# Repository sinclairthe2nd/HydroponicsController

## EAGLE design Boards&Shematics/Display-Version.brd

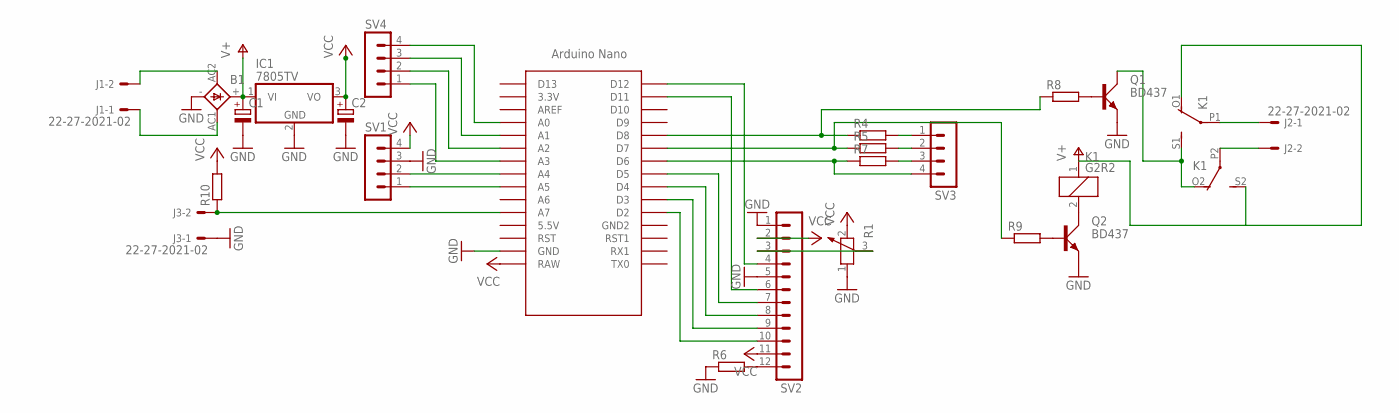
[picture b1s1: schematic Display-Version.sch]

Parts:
B1: FBU4
C1: CPOL-EUE3.5-10; E3,5-10
C2: CPOL-EUE2.5-6; E2,5-6
IC1: 7805TV; TO220V
J1, J2, J3: 22-27-2021-02; 6410-02
K1: G2R2
Q1, Q2: BD437; TO126AV
R1: POTENTIOMETER_PT-10S; PT-10S
R4, R5, R6, R7, R8, R9, R10: R-EU_R1206W; R1206W
SV1, SV3, SV4: MA04-1
SV2: MA12-1
U$1: NANO

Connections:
GND: B1.-, C1.-, C2.-, IC1.2 (GND), J3.1, Q1.E, Q2.E, R1.1, R6.1, SV1.3, SV2.1, SV2.5, U$1.GND
unnamed: R6.2, SV2.12
unnamed: R4.1, R8.1, U$1.D8
unnamed: B1.AC2 (AC1), J1.2
unnamed: B1.AC1 (AC2), J1.1
unnamed: R5.1, R9.1, U$1.D7
unnamed: R4.2, SV3.1
unnamed: R7.1, SV3.4, U$1.D6
unnamed: R5.2, SV3.2
unnamed: R7.2, SV3.3
unnamed: J2.1, K1.P1
unnamed: J2.2, K1.P2
unnamed: Q1.B, R8.2
unnamed: K1.2, Q2.C
unnamed: Q2.B, R9.2
unnamed: SV2.10, U$1.D2
unnamed: SV2.9, U$1.D3
unnamed: SV2.8, U$1.D4
unnamed: SV2.7, U$1.D5
unnamed: SV2.6, U$1.D11
unnamed: SV2.4, U$1.D12
unnamed: R1.3, SV2.3
unnamed: SV1.1, U$1.A5
unnamed: K1.O2 (O), K1.S1 (S), Q1.C
unnamed: SV1.2, U$1.A4
unnamed: SV4.1, U$1.A3
unnamed: J3.2, R10.1, U$1.A7
unnamed: SV4.2, U$1.A2
unnamed: SV4.3, U$1.A1
unnamed: SV4.4, U$1.A0
V+: B1.+, C1.+, IC1.1 (VI), K1.1, K1.O1 (O), K1.S2 (S)
VCC: C2.+, IC1.3 (VO), R1.2, R10.2, SV1.4, SV2.2, SV2.11, U$1.RAW

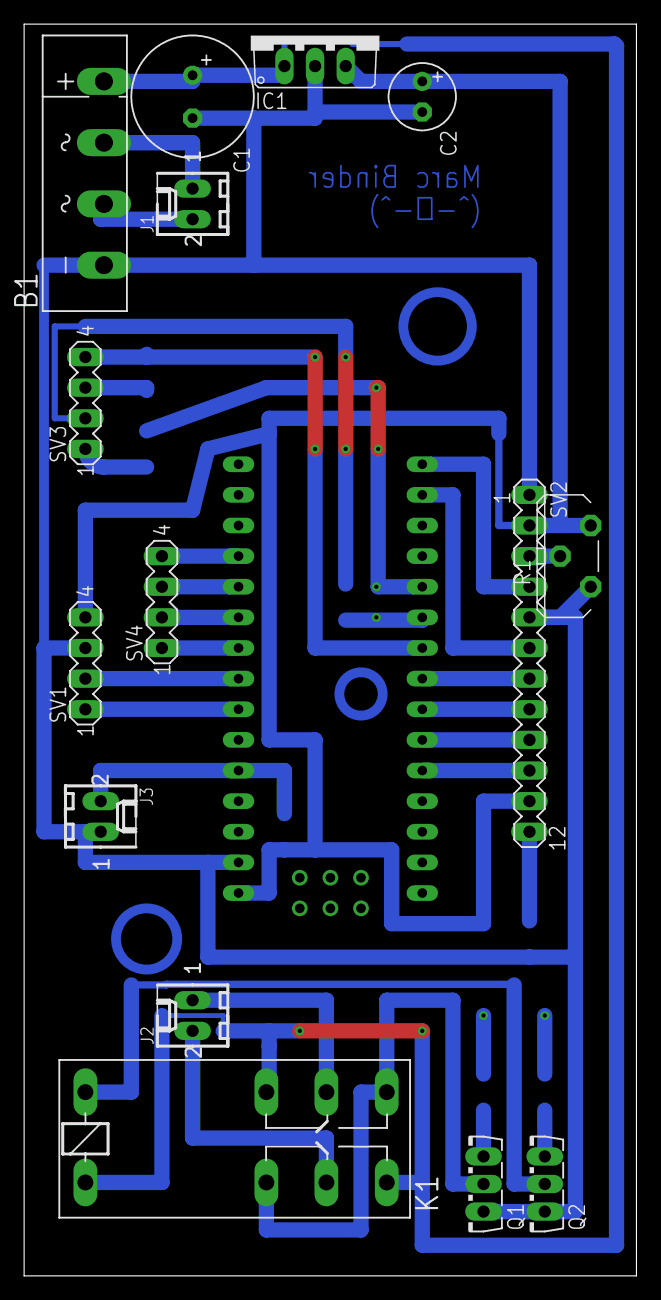
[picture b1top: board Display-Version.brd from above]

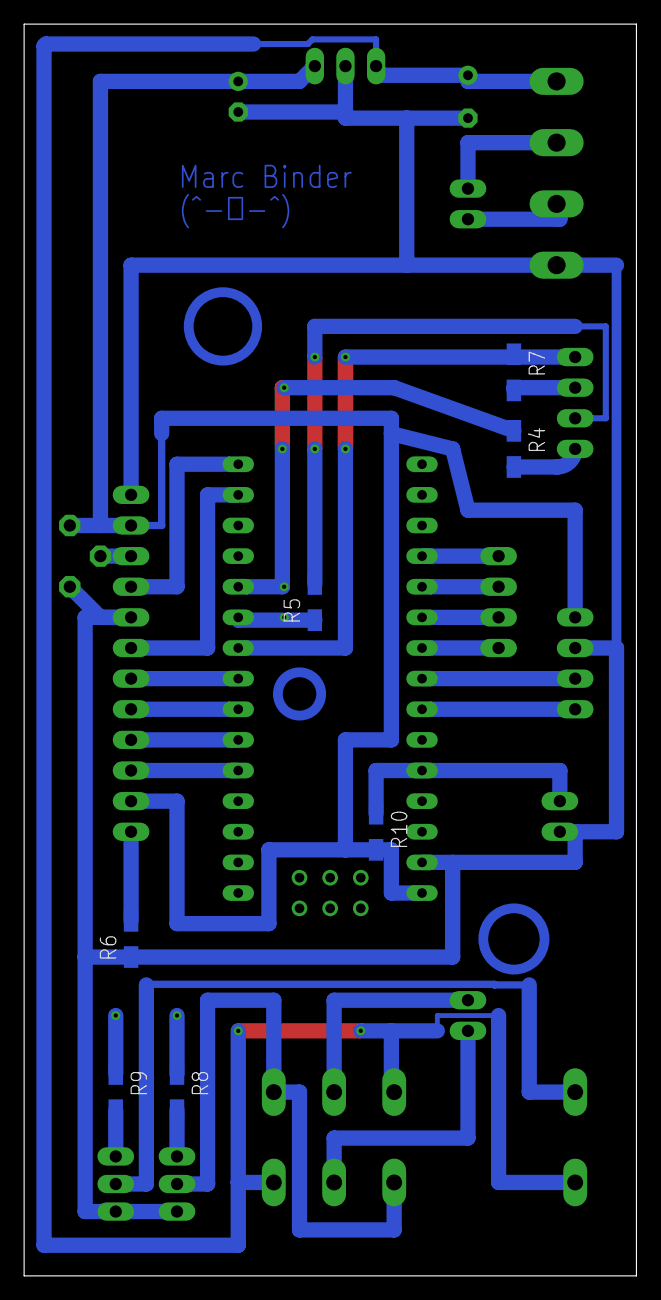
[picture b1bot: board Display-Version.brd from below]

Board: 2 copper layers, 50.8 x 103.8 mm, 23 parts (7 on the bottom side), 32 nets.
